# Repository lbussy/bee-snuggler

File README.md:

# Bee Snuggler

Beats the hell out of tucking them in at night.

## Discussions

Discussions related to minimum viable product for Bee Snuggler, as well as feedback, features, and enhancements are [here](https://github.com/lbussy/bee-snuggler/discussions).

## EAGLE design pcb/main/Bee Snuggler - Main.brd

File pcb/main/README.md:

# Bee Snuggler PCBs

You will need the following for this project:

1. 1 ea. Populated PCB (BOM below)
1. 5 ea. DS18B20 Sensors with Leads: [$9.98/5 @ Amazon](https://smile.amazon.com/Aideepen-DS18B20-Waterproof-Temperature-Stainless/dp/B01LY53CED)
1. 1 ea. Noctua NF-P12 120mm 12VDC PWM Fan: [$13.90 @ Amazon](https://smile.amazon.com/gp/product/B07CG2PGY6)
1. 1 ea. 12 Volt 2A Power Adapter Supply AC to DC 2.1mm X 5.5mm Plug: [$7.99 @ Amazon](https://smile.amazon.com/TMEZON-Power-Adapter-Supply-2-1mm/dp/B00Q2E5IXW)

## PCB BOM:

- 1 ea. PCB: [$33.70/3 @ Osh Park](https://oshpark.com/shared_projects/ufkYhMaZ)
    - 
    - 
- 1 ea Lolin D32 v1.0: [$6.50 @ AliExpress](https://www.aliexpress.com/item/32808551116.html)

1 ea. MLCC - Leaded RAD 50V 0.1uF X7R 10% LS:2.5mm: $0.26 @ Mouser
2 ea. MLCC - Leaded RAD 25V 1uF X7R 10% LS:2.5mm: $0.39 ($0.78) @ Mouser
1 ea. MLCC - Leaded RAD 25V 10uF X7R 10% LS:2.5mm: $0.73 @ Mouser
5 ea. Wurth Pluggable Terminal Blocks Header 691311500103: $0.43 ($2.15) @ Mouser
5 ea. Wurth Pluggable Terminal Blocks Rising Cage 691352510003: $1.71 ($8.55) @ Mouser
Pluggable Terminal Blocks WR-TBL Terminal block - PCB Header - THT	RoHS Compliant		1	$0.57	$0.57
Pluggable Terminal Blocks WR-TBL Terminal block - Plug Rising Cage	RoHS Compliant		1	$1.46	$1.46
Pluggable Terminal Blocks WR-TBL Terminal block - Plug Rising Cage	RoHS Compliant		1	$2.28	$2.28
Headers & Wire Housings 16P STRT BRD MNT SKT 1 ROW 30MICRO" AU	RoHS Compliant		2	$2.73	$5.46
Pluggable Terminal Blocks WR-TBL Terminal block - PCB Header - THT	RoHS Compliant		1	$0.63	$0.63
Carbon Film Resistors - Through Hole 2.2K OHM 5% 1/4W	RoHS Compliant		5	$0.22	$1.10
Linear Voltage Regulators 5 Volt Reg	RoHS Compliant By Exemption		1	$1.79	$1.79
Heat Sinks HEATSINK	RoHS Compliant		1	$0.63	$0.63
DC Power Connectors Power Jack/Connector 2.1mm x 5.5mm	RoHS Compliant		1	$1.00	$1.00

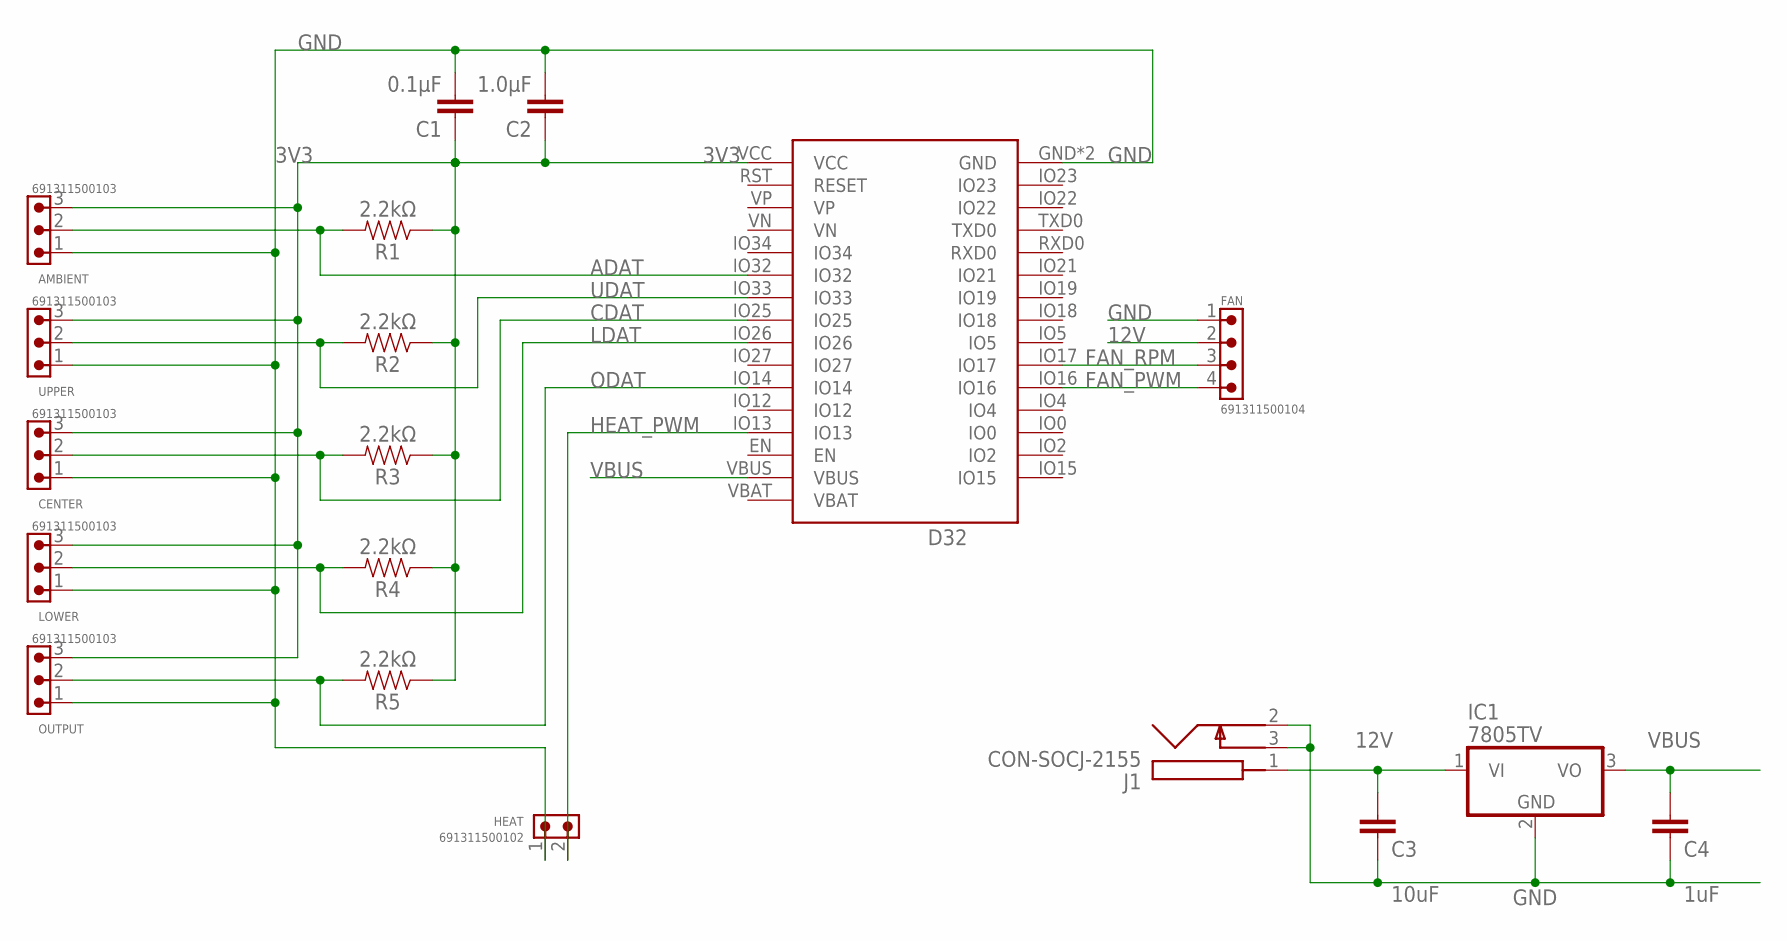
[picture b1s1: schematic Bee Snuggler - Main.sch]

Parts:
AMBIENT: 691311500103
C1: 0.1μF; CAP_PTH-2.54
C2: 1.0μF; CAP_PTH-2.54
C3: 10uF; CAP_PTH-2.54
C4: 1uF; CAP_PTH-2.54
CENTER: 691311500103
D32: Lolin D32; D32_PRO
FAN: 691311500104
HEAT: 691311500102
IC1: 7805TV; TO220V
J1: CON-SOCJ-2155; CONSOCJ2155
LOWER: 691311500103
OUTPUT: 691311500103
R1, R2, R3, R4, R5: 2.2kΩ; AXIAL-0.3
UPPER: 691311500103

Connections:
3V3: AMBIENT.3, C1.1, C2.1, CENTER.3, D32.VCC, LOWER.3, OUTPUT.3, R1.P$1 (1), R2.P$1 (1), R3.P$1 (1), R4.P$1 (1), R5.P$1 (1), UPPER.3
12V: C3.1, FAN.2, IC1.1 (VI), J1.1
ADAT: AMBIENT.2, D32.IO32, R1.P$2 (2)
CDAT: CENTER.2, D32.IO25, R3.P$2 (2)
FAN_PWM: D32.IO16, FAN.4
FAN_RPM: D32.IO17, FAN.3
GND: AMBIENT.1, C1.2, C2.2, C3.2, C4.2, CENTER.1, D32.GND, D32.GND2 (GND), FAN.1, HEAT.1, IC1.2 (GND), J1.2, J1.3, LOWER.1, OUTPUT.1, UPPER.1
HEAT_PWM: D32.IO13, HEAT.2
LDAT: D32.IO26, LOWER.2, R4.P$2 (2)
ODAT: D32.IO14, OUTPUT.2, R5.P$2 (2)
UDAT: D32.IO33, R2.P$2 (2), UPPER.2
VBUS: C4.1, D32.VBUS, IC1.3 (VO)

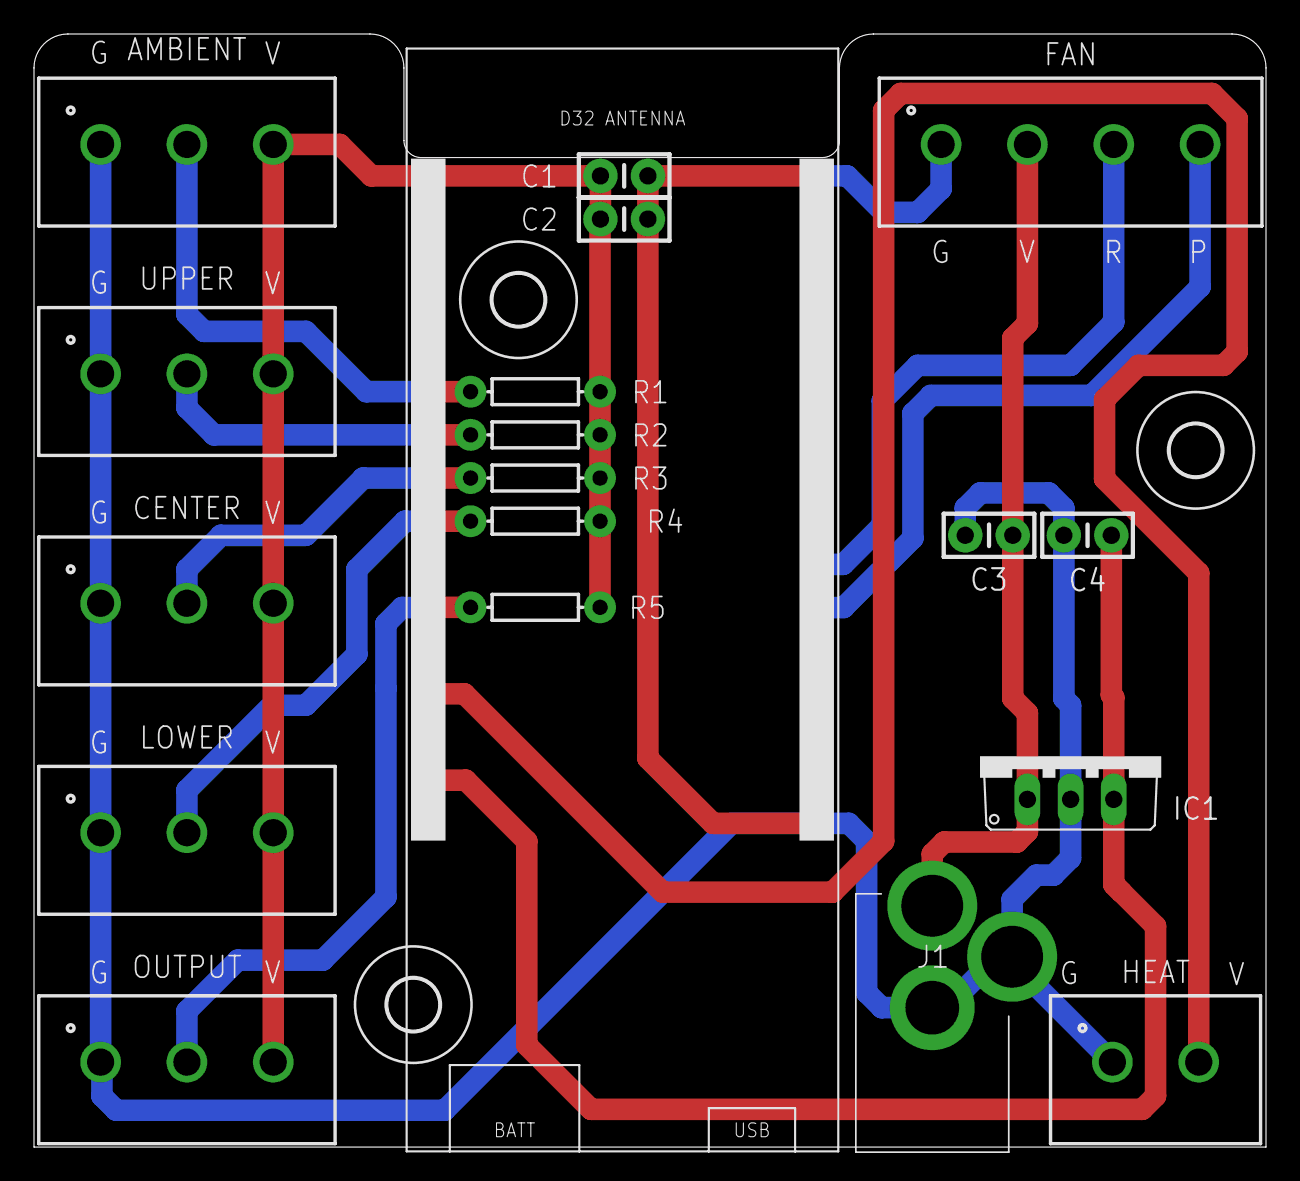
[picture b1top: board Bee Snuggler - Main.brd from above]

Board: 2 copper layers, 72.5 x 65.5 mm, 22 parts (0 on the bottom side), 12 nets.

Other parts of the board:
U$1, U$2, U$3: 3,0

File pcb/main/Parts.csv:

"Part","Value","Device","Package","Description","DATASHEET-URL","IR-UL","IR-VDE","MOUNT","PART-NUMBER","PINS","PITCH","POPULARITY","PROD_ID","TYPE","VALUE","WORKING-VOLTAGE-UL","WORKING-VOLTAGE-VDE";
"AMBIENT"," 691311500103 ","691311500103","691311500103","WR-TBL Serie 311 - 5.08 mm Close Vertical PCB Header","https://www.we-online.com/catalog/datasheet/691311500103.pdf","20A","20A","THT"," 691311500103 "," 3 ","5.08mm","","","Vertical"," 691311500103 ","300V (AC)","300V (AC)";
"C1","0.1μF","CAP_CERAMIC_2.54","CAP_PTH-2.54","","","","","","","","","","","","","","";
"C2","1.0μF","CAP_CERAMIC_2.54","CAP_PTH-2.54","","","","","","","","","","","","","","";
"C3","10uF","CAP_CERAMIC_2.54","CAP_PTH-2.54","","","","","","","","","","","","","","";
"C4","1uF","CAP_CERAMIC_2.54","CAP_PTH-2.54","","","","","","","","","","","","","","";
"CENTER"," 691311500103 ","691311500103","691311500103","WR-TBL Serie 311 - 5.08 mm Close Vertical PCB Header","https://www.we-online.com/catalog/datasheet/691311500103.pdf","20A","20A","THT"," 691311500103 "," 3 ","5.08mm","","","Vertical"," 691311500103 ","300V (AC)","300V (AC)";
"CN1","","DCBARRELPTH","DCJACK_2MM_PTH","2.0mm DC Barrel Jack","","","","","","","","","","","","","";
"D32","Lolin D32","WEMOS-D32D32_PRO","D32_PRO","D32_REVERSE is a Reverse silkscreen for placing the Wemos D32 on the underside of the board","","","","","","","","","","","","","";
"FAN"," 691311500104 ","691311500104","691311500104","WR-TBL Serie 311 - 5.08 mm Close Vertical PCB Header","https://www.we-online.com/catalog/datasheet/691311500104.pdf","20A","20A","THT"," 691311500104 "," 4 ","5.08mm","","","Vertical"," 691311500104 ","300V (AC)","300V (AC)";
"HEAT"," 691311500102 ","691311500102","691311500102","WR-TBL Serie 311 - 5.08 mm Close Vertical PCB Header","https://www.we-online.com/catalog/datasheet/691311500102.pdf","20A","20A","THT"," 691311500102 "," 2 ","5.08mm","","","Vertical"," 691311500102 ","300V (AC)","300V (AC)";
"IC1","7805TV","7805TV","TO220V","Positive VOLTAGE REGULATOR","","","","","","","","57","","","","","";
"LOWER"," 691311500103 ","691311500103","691311500103","WR-TBL Serie 311 - 5.08 mm Close Vertical PCB Header","https://www.we-online.com/catalog/datasheet/691311500103.pdf","20A","20A","THT"," 691311500103 "," 3 ","5.08mm","","","Vertical"," 691311500103 ","300V (AC)","300V (AC)";
"OUTPUT"," 691311500103 ","691311500103","691311500103","WR-TBL Serie 311 - 5.08 mm Close Vertical PCB Header","https://www.we-online.com/catalog/datasheet/691311500103.pdf","20A","20A","THT"," 691311500103 "," 3 ","5.08mm","","","Vertical"," 691311500103 ","300V (AC)","300V (AC)";
"R1","2.2kΩ","RESISTORAXIAL-0.3","AXIAL-0.3","Generic Resistor Package","","","","","","","",""," ",""," ","","";
"R2","2.2kΩ","RESISTORAXIAL-0.3","AXIAL-0.3","Generic Resistor Package","","","","","","","",""," ",""," ","","";
"R3","2.2kΩ","RESISTORAXIAL-0.3","AXIAL-0.3","Generic Resistor Package","","","","","","","",""," ",""," ","","";
"R4","2.2kΩ","RESISTORAXIAL-0.3","AXIAL-0.3","Generic Resistor Package","","","","","","","",""," ",""," ","","";
"R5","2.2kΩ","RESISTORAXIAL-0.3","AXIAL-0.3","Generic Resistor Package","","","","","","","",""," ",""," ","","";
"UPPER"," 691311500103 ","691311500103","691311500103","WR-TBL Serie 311 - 5.08 mm Close Vertical PCB Header","https://www.we-online.com/catalog/datasheet/691311500103.pdf","20A","20A","THT"," 691311500103 "," 3 ","5.08mm","","","Vertical"," 691311500103 ","300V (AC)","300V (AC)";

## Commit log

2021-11-28 Initial code commit

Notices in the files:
parts and their libraries:
SparkFun-Resistors: Licensing: Creative Commons ShareAlike 4.0 International - https://creativecommons.org/licenses/by-sa/4.0
Wurth_Connectors_WR-TBL Pluggable Connec: Copyright: Würth Elektronik
